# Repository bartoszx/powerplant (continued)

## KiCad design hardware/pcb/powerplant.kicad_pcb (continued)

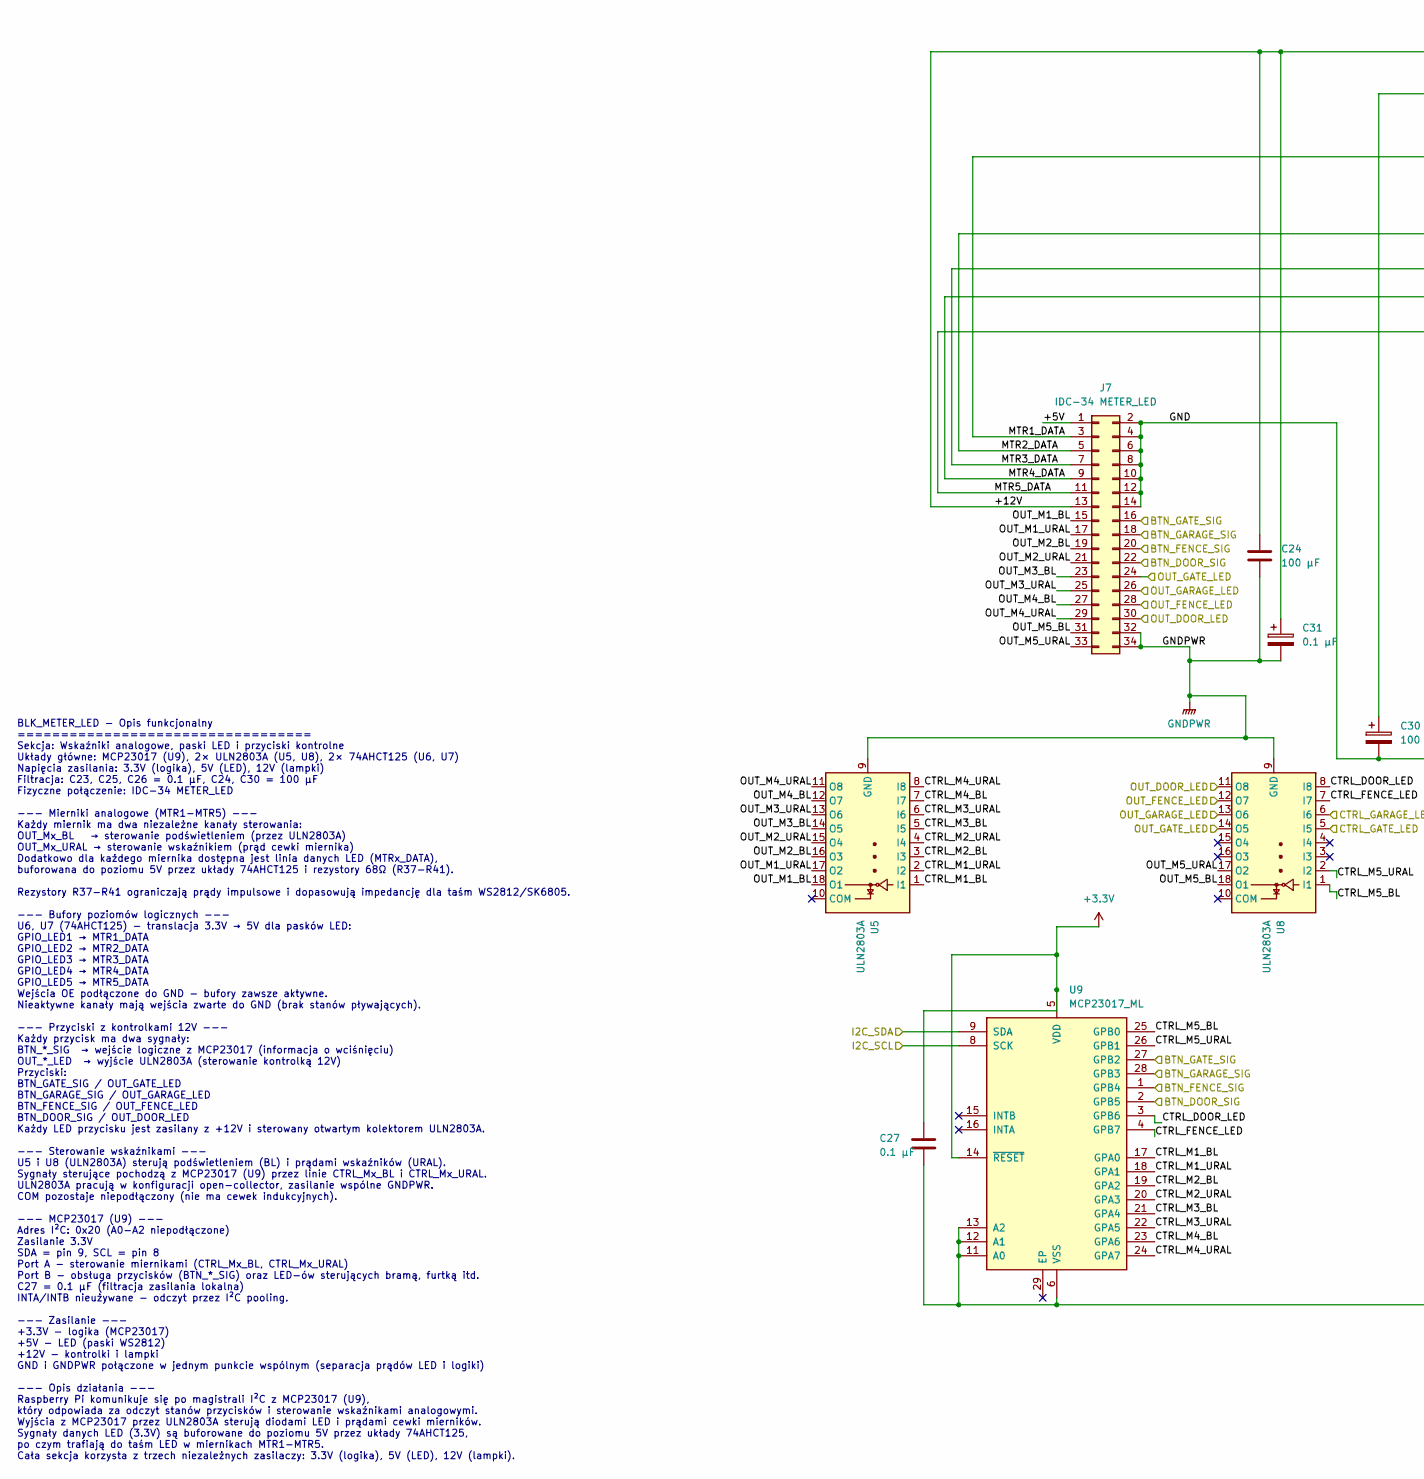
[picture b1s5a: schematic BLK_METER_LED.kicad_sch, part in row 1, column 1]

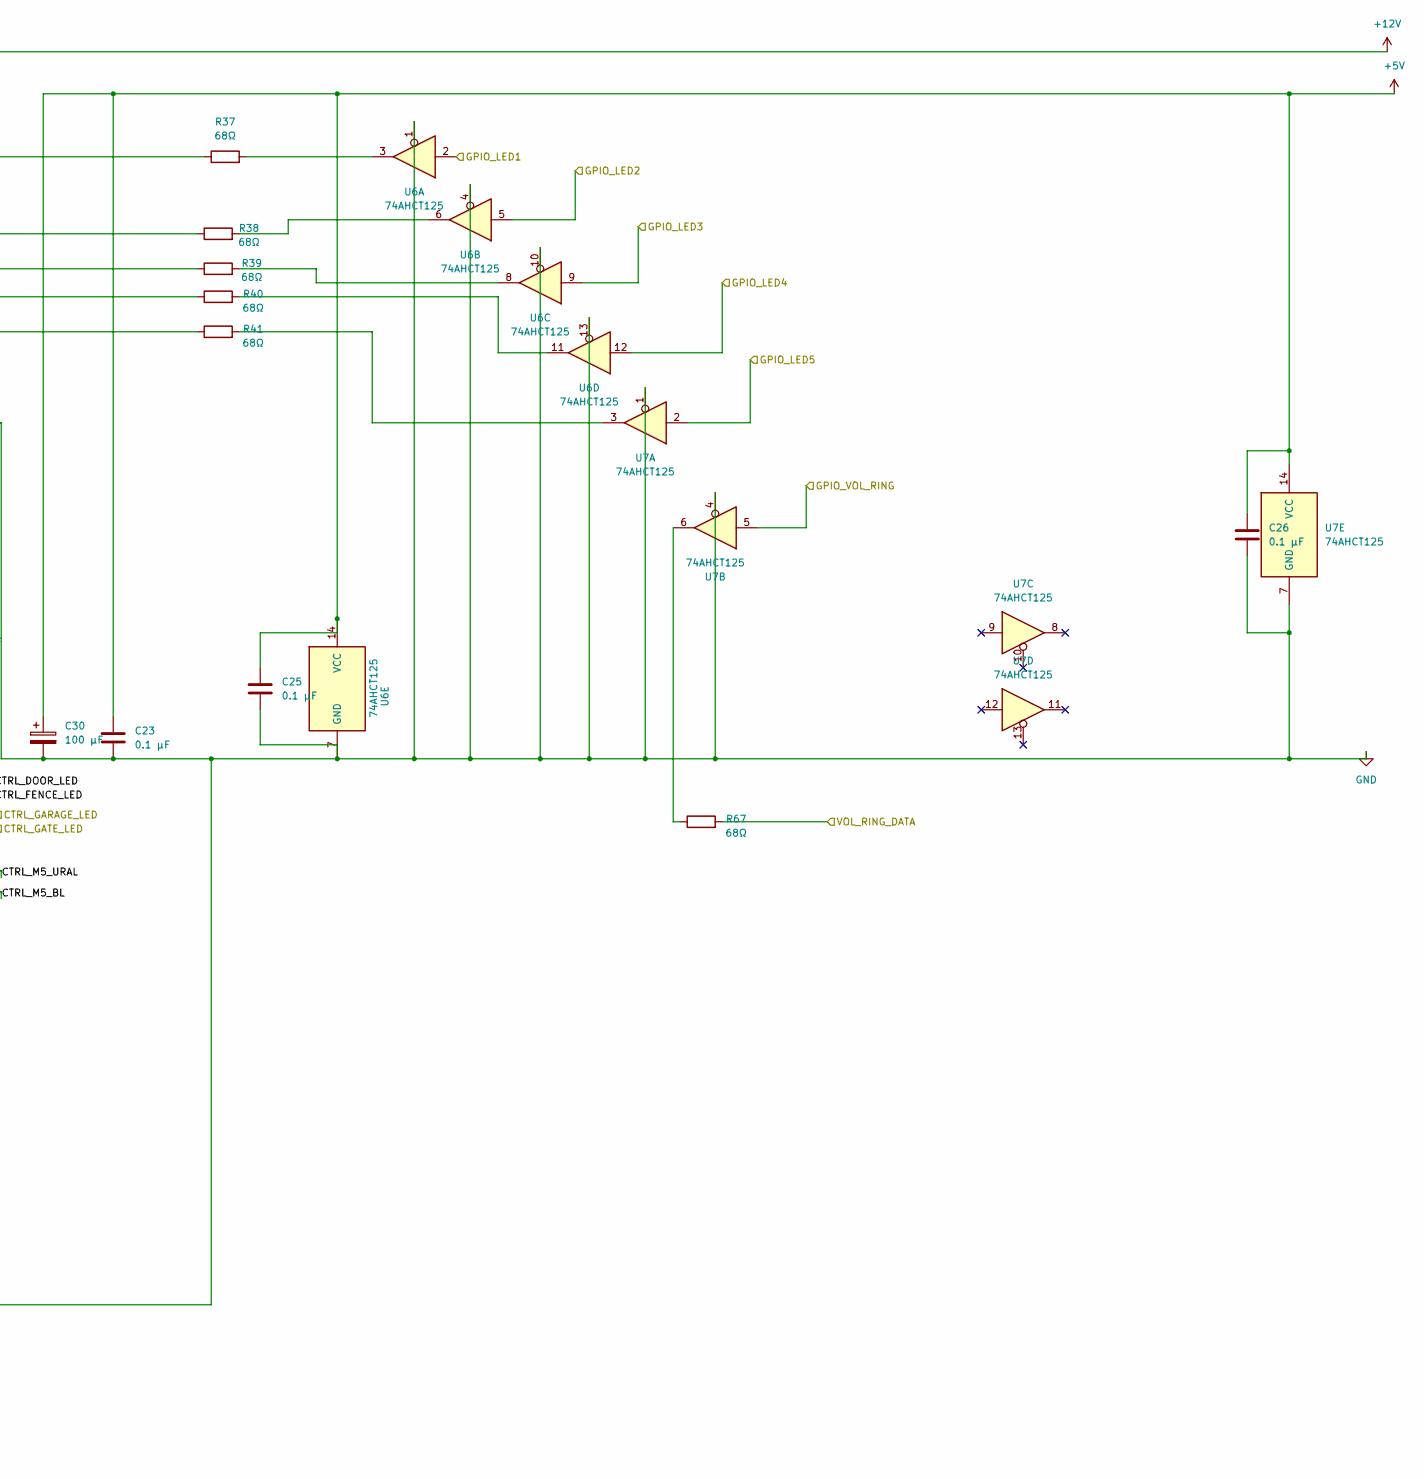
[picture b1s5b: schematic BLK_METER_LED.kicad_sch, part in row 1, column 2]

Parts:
C23, C25, C26, C27: 0.1 µF; C_1206_3216Metric_Pad1.33x1.80mm_HandSolder
C24, C30: 100 µF; CP_Radial_D5.0mm_P2.50mm
C31: 0.1 µF; C_1206_3216Metric
J7: IDC-34 METER_LED; IDC-Header_2x17_P2.54mm_Vertical
R37, R38, R39, R40, R41, R67: 68Ω; R_1206_3216Metric_Pad1.30x1.75mm_HandSolder
U5, U8: ULN2803A; SOIC-18W_7.5x11.6mm_P1.27mm
U6, U7: 74AHCT125; SOIC-14_3.9x8.7mm_P1.27mm
U9: MCP23017_ML; QFN-28-1EP_6x6mm_P0.65mm_EP4.25x4.25mm

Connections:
+3.3V: C27.2, U9.5 (VDD), U9.14 (~RESET); also elsewhere on the board
+5V: C23.2, C25.2, C26.2, C30.1, J7.1, U6.14 (VCC), U7.14 (VCC); also elsewhere on the board
+12V: C24.2, C31.1, J7.13; also elsewhere on the board
/AUX_SCL: U9.8 (SCK); also elsewhere on the board
/AUX_SDA: U9.9 (SDA); also elsewhere on the board
/BLK_BUTTONS/BTN_DOOR_SIG: J7.22, U9.2 (GPB5); also elsewhere on the board
/BLK_BUTTONS/BTN_FENCE_SIG: J7.20, U9.1 (GPB4); also elsewhere on the board
/BLK_BUTTONS/BTN_GARAGE_SIG: J7.18, U9.28 (GPB3); also elsewhere on the board
/BLK_BUTTONS/BTN_GATE_SIG: J7.16, U9.27 (GPB2); also elsewhere on the board
/BLK_BUTTONS/OUT_DOOR_LED: J7.30, U8.11 (O8)
/BLK_BUTTONS/OUT_FENCE_LED: J7.28, U8.12 (O7)
/BLK_BUTTONS/OUT_GARAGE_LED: J7.26, U8.13 (O6)
/BLK_BUTTONS/OUT_GATE_LED: J7.24, U8.14 (O5)
/BLK_CONSOLE/VOL_RING_DATA: R67.2; also elsewhere on the board
/BLK_METER_LED/CTRL_DOOR_LED: U8.8 (I8), U9.3 (GPB6)
/BLK_METER_LED/CTRL_FENCE_LED: U8.7 (I7), U9.4 (GPB7)
/BLK_METER_LED/CTRL_GARAGE_LED: U8.6 (I6); also elsewhere on the board
/BLK_METER_LED/CTRL_GATE_LED: U8.5 (I5); also elsewhere on the board
/BLK_METER_LED/CTRL_M1_BL: U5.1 (I1), U9.17 (GPA0)
/BLK_METER_LED/CTRL_M1_URAL: U5.2 (I2), U9.18 (GPA1)
/BLK_METER_LED/CTRL_M2_BL: U5.3 (I3), U9.19 (GPA2)
/BLK_METER_LED/CTRL_M2_URAL: U5.4 (I4), U9.20 (GPA3)
/BLK_METER_LED/CTRL_M3_BL: U5.5 (I5), U9.21 (GPA4)
/BLK_METER_LED/CTRL_M3_URAL: U5.6 (I6), U9.22 (GPA5)
/BLK_METER_LED/CTRL_M4_BL: U5.7 (I7), U9.23 (GPA6)
/BLK_METER_LED/CTRL_M4_URAL: U5.8 (I8), U9.24 (GPA7)
/BLK_METER_LED/CTRL_M5_BL: U8.1 (I1), U9.25 (GPB0)
/BLK_METER_LED/CTRL_M5_URAL: U8.2 (I2), U9.26 (GPB1)
/BLK_METER_LED/GPIO_LED1: U6.2; also elsewhere on the board
/BLK_METER_LED/GPIO_LED2: U6.5; also elsewhere on the board
/BLK_METER_LED/GPIO_LED3: U6.9; also elsewhere on the board
/BLK_METER_LED/GPIO_LED4: U6.12; also elsewhere on the board
/BLK_METER_LED/GPIO_LED5: U7.2; also elsewhere on the board
/BLK_METER_LED/GPIO_VOL_RING: U7.5; also elsewhere on the board
/BLK_METER_LED/MTR1_DATA: J7.3, R37.1
/BLK_METER_LED/MTR2_DATA: J7.5, R38.1
/BLK_METER_LED/MTR3_DATA: J7.7, R39.1
/BLK_METER_LED/MTR4_DATA: J7.9, R40.1
/BLK_METER_LED/MTR5_DATA: J7.11, R41.1
/BLK_METER_LED/OUT_M1_BL: J7.15, U5.18 (O1)
/BLK_METER_LED/OUT_M1_URAL: J7.17, U5.17 (O2)
/BLK_METER_LED/OUT_M2_BL: J7.19, U5.16 (O3)
/BLK_METER_LED/OUT_M2_URAL: J7.21, U5.15 (O4)
/BLK_METER_LED/OUT_M3_BL: J7.23, U5.14 (O5)
/BLK_METER_LED/OUT_M3_URAL: J7.25, U5.13 (O6)
/BLK_METER_LED/OUT_M4_BL: J7.27, U5.12 (O7)
/BLK_METER_LED/OUT_M4_URAL: J7.29, U5.11 (O8)
/BLK_METER_LED/OUT_M5_BL: J7.31, U8.18 (O1)
/BLK_METER_LED/OUT_M5_URAL: J7.33, U8.17 (O2)
GND: C23.1, C25.1, C26.1, C27.1, C30.2, J7.2, J7.4, J7.6, J7.8, J7.10, J7.12, J7.14, U6.1, U6.4, U6.7 (GND), U6.10, U6.13, U7.1, U7.4, U7.7 (GND), U9.6 (VSS), U9.11 (A0), U9.12 (A1), U9.13 (A2); also elsewhere on the board
GNDPWR: C24.1, C31.2, J7.32, J7.34, U5.9 (GND), U8.9 (GND); also elsewhere on the board
unnamed: R37.2, U6.3
unnamed: R38.2, U6.6
unnamed: R39.2, U6.8
unnamed: R40.2, U6.11
unnamed: R41.2, U7.3
unnamed: R67.1, U7.6

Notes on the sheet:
BLK_METER_LED - Opis funkcjonalny ================================== Sekcja: Wskaźniki analogowe, paski LED i przyciski kontrolne Układy główne: MCP23017 (U9), 2× ULN2803A (U5, U8), 2× 74AHCT125 (U6, U7) Napięcia zasilania: 3.3V (logika), 5V (LED), 12V (lampki) Filtracja: C23, C25, C26 = 0.1 µF, C2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

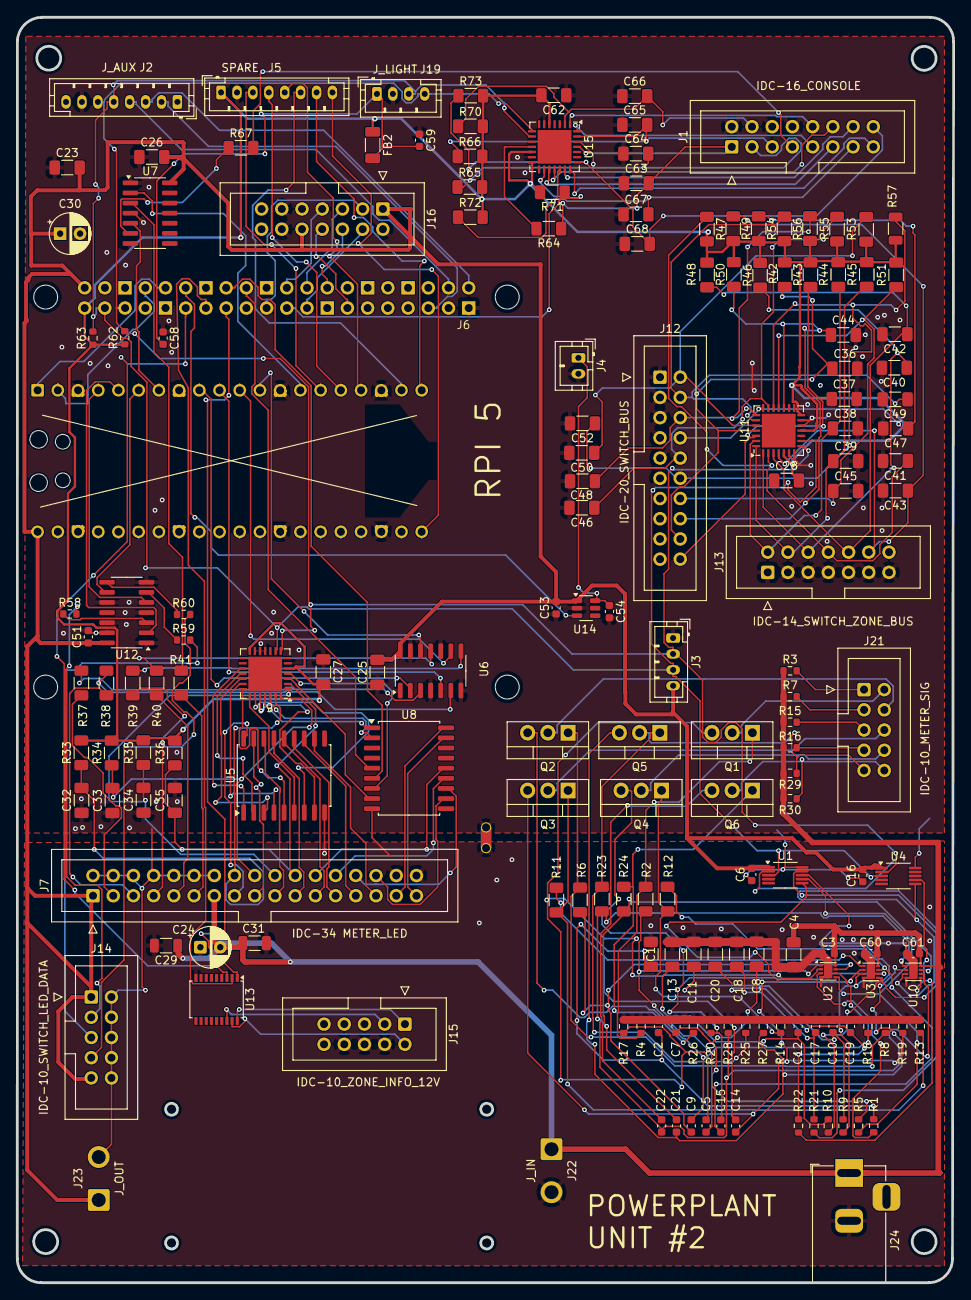
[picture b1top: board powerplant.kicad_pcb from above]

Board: 2 copper layers, 117.6 x 159.0 mm, 174 parts (1 on the bottom side), 162 nets.

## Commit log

2025-10-20 init
2026-05-25 Update hardware schematics and documentation; added source of truth for hardware, removed unused symbols, and modified connector specifications.
2026-05-29 Update .gitignore to exclude report files and enhance README with details on the measurement module and related documentation.
